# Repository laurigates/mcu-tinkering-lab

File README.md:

# MCU Tinkering Lab

A monorepo of microcontroller projects, mostly ESP32. The largest is a robot car
that drives on camera input and an LLM's plan. Others cover audio toys, game
controller bridges, an ESP-NOW mesh of companion boxes, and a self-balancing
robot on the RP2350.

## Flash from the browser

Released firmware can be flashed with the
[web flasher](https://laurigates.github.io/mcu-tinkering-lab/) in Chrome or
Edge, with no toolchain installed. Board-specific boot-mode notes are on the
page itself ([source](docs/flasher/index.html)).

The [robocar board story](https://laurigates.github.io/mcu-tinkering-lab/robocar/)
follows the robot car from a 2018 kit to a generated, factory-made carrier
board ([source](docs/site/robocar/index.html)).

## Build from source

ESP-IDF builds run in a container, so Docker and
[just](https://github.com/casey/just) are the only requirements.

```bash
git clone https://github.com/laurigates/mcu-tinkering-lab.git
cd mcu-tinkering-lab
just setup-all                   # Docker images, dev tools, pre-commit hooks
just list-projects               # every project module
just robocar::build              # build one
```

Build, test and CI details are in [CONTRIBUTING.md](CONTRIBUTING.md).

## Projects

| Domain | Projects |
|---|---|
| `robotics/` | [AI robot car](packages/robotics/robocar/README.md): single-board firmware (XIAO ESP32-S3 Sense), its [integrated carrier](packages/robotics/robocar/integrated/README.md), [bring-up self-test](packages/robotics/robocar/bringup/README.md), a [Pymunk plant model](packages/robotics/robocar/simulation/README.md) and a [behaviour twin](packages/robotics/robocar/twin/README.md). [Self-balancing robot](packages/robotics/balancebot/README.md) (XIAO RP2350, Pico SDK) |
| `thinkpack/` | ESP-NOW mesh of companion boxes: brainbox (LLM coordinator), boombox, chatterbox, finderbox, glowbug, mesh-demo |
| `camera-vision/` | MJPEG webserver, camera + I2S audio, LLM Telegram bot, Gemini object detection |
| `audio/` | BLE gamepad synth, kids' audio toy, melody detector, RFID audiobook player (ESPHome) |
| `input-gaming/` | Xbox → Switch bridge, Switch USB proxy, LEGO Boost with an Xbox controller |
| `networking/` | IT troubleshooter, WiFi AP test, WireGuard + Home Assistant (ESPHome) |
| `sensors/` | 24 GHz mmWave presence sensor (ESPHome) |
| `usb-tools/` | ESP32-S3 raw USB relay for facedancer |
| `games/` | NFC scavenger hunt |
| `components/` | Shared ESP-IDF components: Improv WiFi provisioning, GitHub Releases OTA, ThinkPack libraries |

Most projects have a README in their directory.

## Documentation

- [docs/](docs/README.md): architecture decisions, requirements, board
  references, schematics
- [CONTRIBUTING.md](CONTRIBUTING.md): development setup, build commands,
  testing, CI, adding a project

## License

MIT ([LICENSE](LICENSE)), except the two vendored KiCad libraries under
`tools/kicad/lib/`, which keep their upstream licences:
[`kicad-stock/`](tools/kicad/lib/kicad-stock/) is a subset of the KiCad
libraries under CC-BY-SA 4.0 with KiCad's design exception
([LICENSE.md](tools/kicad/lib/kicad-stock/LICENSE.md)), and
[`seeed-xiao/`](tools/kicad/lib/seeed-xiao/) is Seeed Studio's, under their MIT
licence ([LICENSE](tools/kicad/lib/seeed-xiao/LICENSE)).

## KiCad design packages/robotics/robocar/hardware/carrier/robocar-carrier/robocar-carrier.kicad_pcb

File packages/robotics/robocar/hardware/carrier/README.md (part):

# robocar carrier PCB

> **Before paying for an order**, Lauri does the bench checks in
> [Pre-order checks still owed](#pre-order-checks-still-owed-lauri);
> [`board.toml`](board.toml) marks every unmeasured dimension (#750).

One 100 × 100 mm, 2-layer PCB that carries four pieces and replaces the
hand-wired harness in [`WIRING.md`](../../WIRING.md):

- the **main board**, x 0–70.5 mm, screwed to the chassis (no ready-made plate; the chassis is drilled to match H1–H4): the motor driver,
  the PWM driver, the I2C mux, the GPIO expander and its mirror header, the
  amplifier, the 3V3 regulator, the power and peripheral connectors, the
  buzzer and the test headers;
- three **head boards** in a column on its right, each 29.5 × 29.5 mm, for the
  pan-tilt kit's top cradle: a XIAO ESP32-S3 Sense socket and the head end of
  the ribbon. They differ only in where the ribbon header sits (see
  [The three heads](#the-three-heads)); fit the XIAO to the one that suits the
  cradle.

Copper-free bands of 3 mm or more under silkscreen saw lines ("CUT", on both
faces) separate the pieces. JLCPCB makes one rectangle with no V-cuts, tabs or
slots; the pieces are sawn apart after delivery (see
[Separating the pieces](#separating-the-pieces)). A 2 × 7, 2.0 mm-pitch IDC
ribbon joins the main board to the fitted head.

KiCad 10 project: [`robocar-carrier/`](robocar-carrier/). Its
schematic is generated from [`hardware.toml`](../../hardware.toml) and the parts
registry ([`docs/reference/parts/`](../../../../../docs/reference/parts/)) by
`tools/kicad`
([ADR-027](../../../../../docs/decisions/ADR-027-kicad-carrier-generation.md));
the board is placed and routed from the same netlist and
[`board.toml`](board.toml), which holds every position, the bands and the
silkscreen. Never edit the `.kicad_sch` or `.kicad_pcb` in KiCad; change those
files and regenerate (see [Regenerate and check](#regenerate-and-check)).

## What is on it

Each module sits in female headers or plugs into a connector, so any of them can
be swapped without desoldering. The passives and the regulator are SMD on the
top side; everything else is through-hole.

| Ref | Part | Board | Notes |
|---|---|---|---|
| U1, U3, U4 | XIAO ESP32-S3 Sense socket, two 1×7 female headers | heads 1, 2, 3 | USB-C toward the head's top edge; fit one XIAO |
| J2, J16, J17 | 2×7 pin header, 2.0 mm, unshrouded | heads 1, 2, 3 | The head end of the ribbon; see [The three heads](#the-three-heads) |
| H5–H10 | M2 holes, 2.2 mm, ISO 7380 courtyard | heads 1, 2, 3 | Through the cradle into heat-set inserts; M2 button heads only |
| J1 | 2×7 pin header, 2.0 mm, unshrouded | main | The main end of the ribbon, in the front row; its pins are 21–33 mm in from the main board's right edge. Lauri's 10–15 cm ribbon length was for J1's earlier spot beside the head column, so check it still reaches |
| A1 | SparkFun TB6612FNG, in 2 × 1×8 female headers | main | Motor outputs on its left header |
| A2 | Adafruit PCA9685, in female headers on its JP3 side header and its channel 8–13 PWM pins | main | Motor control lines; servo and LED columns stay on the module |
| A3 | Adafruit TCA9548A, or the wider purple TCA9548A/PCA9548A clone, in female headers | main | Every I2C device sits behind it. The clone's rows are one pitch wider, so the upstream (VIN…SC1) side has a second row of holes one pitch toward the rear, each joined to the hole beside it; see [The TCA9548A socket](#the-tca9548a-socket) |
| A4 | Adafruit MAX98357A, in a 1×7 female header | main | The speaker stays on the module's terminal |
| A5 | CJMCU-2317 (MCP23017), in female headers under all 30 holes | main | On mux channel 2, address 0x20; see [The GPIO expander](#the-gpio-expander) |
| J18 | 2×10 pin header, 2.54 mm | main | The expander's GPIOs, in the module's own order; see [The GPIO expander](#the-gpio-expander) |
| U2 | AMS1117-3.3, SOT-223 | main | The main board's 3V3; the XIAO's 3V3 pad stays open |
| D1 | B5819W Schottky, SOD-123 | main | Between the main board's 5V and the ribbon's 5V conductors (net `XIAO_5V`), beside J1: the XIAO's 5V pad is its USB-C VBUS |
| C1–C3 | 470 µF 16 V electrolytic, 8 × 10.5 mm | main | Bulk on the 5V trunk for the PCA9685 V+ and TB6612FNG VM (C1, C2), and beside the MAX98357A Vin (C3) |
| C4–C6 | 100 nF, 0805 | main | PCA9685 VCC, TCA9548A VIN, MCP23017 VCC (C6, beside the CJMCU-2317's socket) |
| C7, C8 | 22 µF 16 V tantalum, 3528 | main | AMS1117 input and output |
| R1 | 100 Ω, 0805 | main | Buzzer series resistor |
| R2–R11 | 2.2 kΩ, 0805 | main | Pull-ups on mux channels 0–4 (R10, R11 on channel 2); see [Pre-fab review](#pre-fab-review-810) |
| R12, R13 | 2.2 kΩ, 0805 | main | Pull-ups on the upstream I2C bus (the XIAO's SDA and SCL), beside C5 in the row behind A3 |
| F1 | 4 A hold PTC fuse, 16 V, 1812 (BSMD1812-400-16V) | main | Between J3 and everything else, beside J3 |
| J3 | XT30 (AMASS XT30PW-M) | main | Pack in; pad 1 is "−" |
| J4 | JST VH 4-pin (B4P-VH), 3.96 mm | main | LM2596 module: IN+, IN−, OUT+, OUT−; the silkscreen prints "I+ I- O+ O-" and "SET LM2596 TO 5.0V FIRST" beside it |
| J5, J6 | JST-XH 2-pin | main | Left and right motor, side by side at A1's motor outputs |
| J7, J8 | JST-XH 4-pin | main | RCWL-1601 front and rear, I2C mode: VCC, SCL, SDA, GND (silkscreen "V C D G"); side by side at the front edge |
| J9 | JST-XH 4-pin | main | SSD1306 0.91" OLED: GND, VCC, SCL, SDA (silkscreen "G V C D") |
| BZ1 | 12 mm buzzer, 7.6 mm pin pitch | main | Soldered to the board; + on pad 1, beside the silkscreen "+" |
| J11–J15 | 1×4 and 1×2 pin headers | main | Test headers, see [Debug headers](#debug-headers) |
| H1–H4 | M3 holes | main | Chassis (drilled to match) |

The per-part values, LCSC numbers and the reasons for each are in
[`hardware.toml`](../../hardware.toml); the pin orders are in the registry entries
it names.

## The three heads

All three have the same outline, the same two M2 holes in the top corners
(22.5 mm apart, the positions Lauri confirmed on 2026-10-16), and the XIAO with
its USB-C toward the top edge, which points the Sense camera forward. The
cradle's sides carry clips, so the header sits at the top or the bottom edge,
never at a side (Lauri, 2026-10-16). Only one head gets a XIAO; the other two
stay spare.

| Head | Refs | Header | XIAO | For |
|---|---|---|---|---|
| 1 | U1, J2, H5, H6 | Back face, bottom edge | Between the holes, above the header | The plug and ribbon behind the head, leaving the bottom edge |
| 2 | U3, J16, H7, H8 | Front face, bottom edge | Between the holes, above the header | The plug in front, below the camera, if nothing behind the head clears it |
| 3 | U4, J17, H9, H10 | Back face, top edge, between the holes | Below the holes | The ribbon leaving over the top, if the bottom edge is blocked |

The holes use KiCad's ISO 7380 M2 footprint, whose courtyard is a 3.5 mm button
head: on heads 1 and 2 the XIAO socket sits 0.26 mm from it on each side. Fit
M2 button-head screws (ISO 7380) or another head no larger than 3.5 mm.

Each head's spare copy of the XIAO socket is wired to its own header (nets
`HEAD2_*`, `HEAD3_*`); the main board has a single end, J1. Moving the ribbon
to another head moves the robot to it.

## The ribbon survives a reversed plug

The headers are unshrouded 2.0 mm-pitch pin headers, mated by a 2.0 mm IDC plug
on 1.0 mm-pitch flat ribbon. The plug fits either way round, which takes
pin *n* to pin 15 − *n*. The pinout in
[`idc-2x07-xiao-cable.toml`](../../../../../docs/reference/parts/idc-2x07-xiao-cable.toml)
pairs each pin with one it can safely swap with: 5 V lands on 5 V, GND on GND,
SDA on SCL, UART0 TX on the unconnected pin 9, and every other XIAO output on
another main-board input. **A reversed plug damages nothing and does not work.**
If the robot is dead after reassembly, check the plug orientation first: every
header prints a pin-1 mark.

## The GPIO expander

The CJMCU-2317 module (A5) sits in female headers under all 30 of its holes,
so it plugs in firmly and every pin reaches the board. It is turned 180°: its
single column (I2C and supply) faces the mux, its double column of GPIOs faces
the right edge. Hole positions and which column is which are Lauri's
measurement of the fitted module (2026-10-16), recorded on
[its board page](../../../../../docs/reference/boards/cjmcu-2317.md).
It fits upside down too, which shorts 3V3: fit it chip side up (see
[Assembly notes](#assembly-notes)). The silkscreen inside its socket outline
names every hole, and "CHIP SIDE UP" is printed below it.

- **Address 0x20, hard-strapped.** A0, A1 and A2 go straight to GND, which is
  `MCP23017_ADDR` in [`main/pin_config.h`](../../main/pin_config.h). A direct
  tie overrides whatever bias the module itself puts on those pins.
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
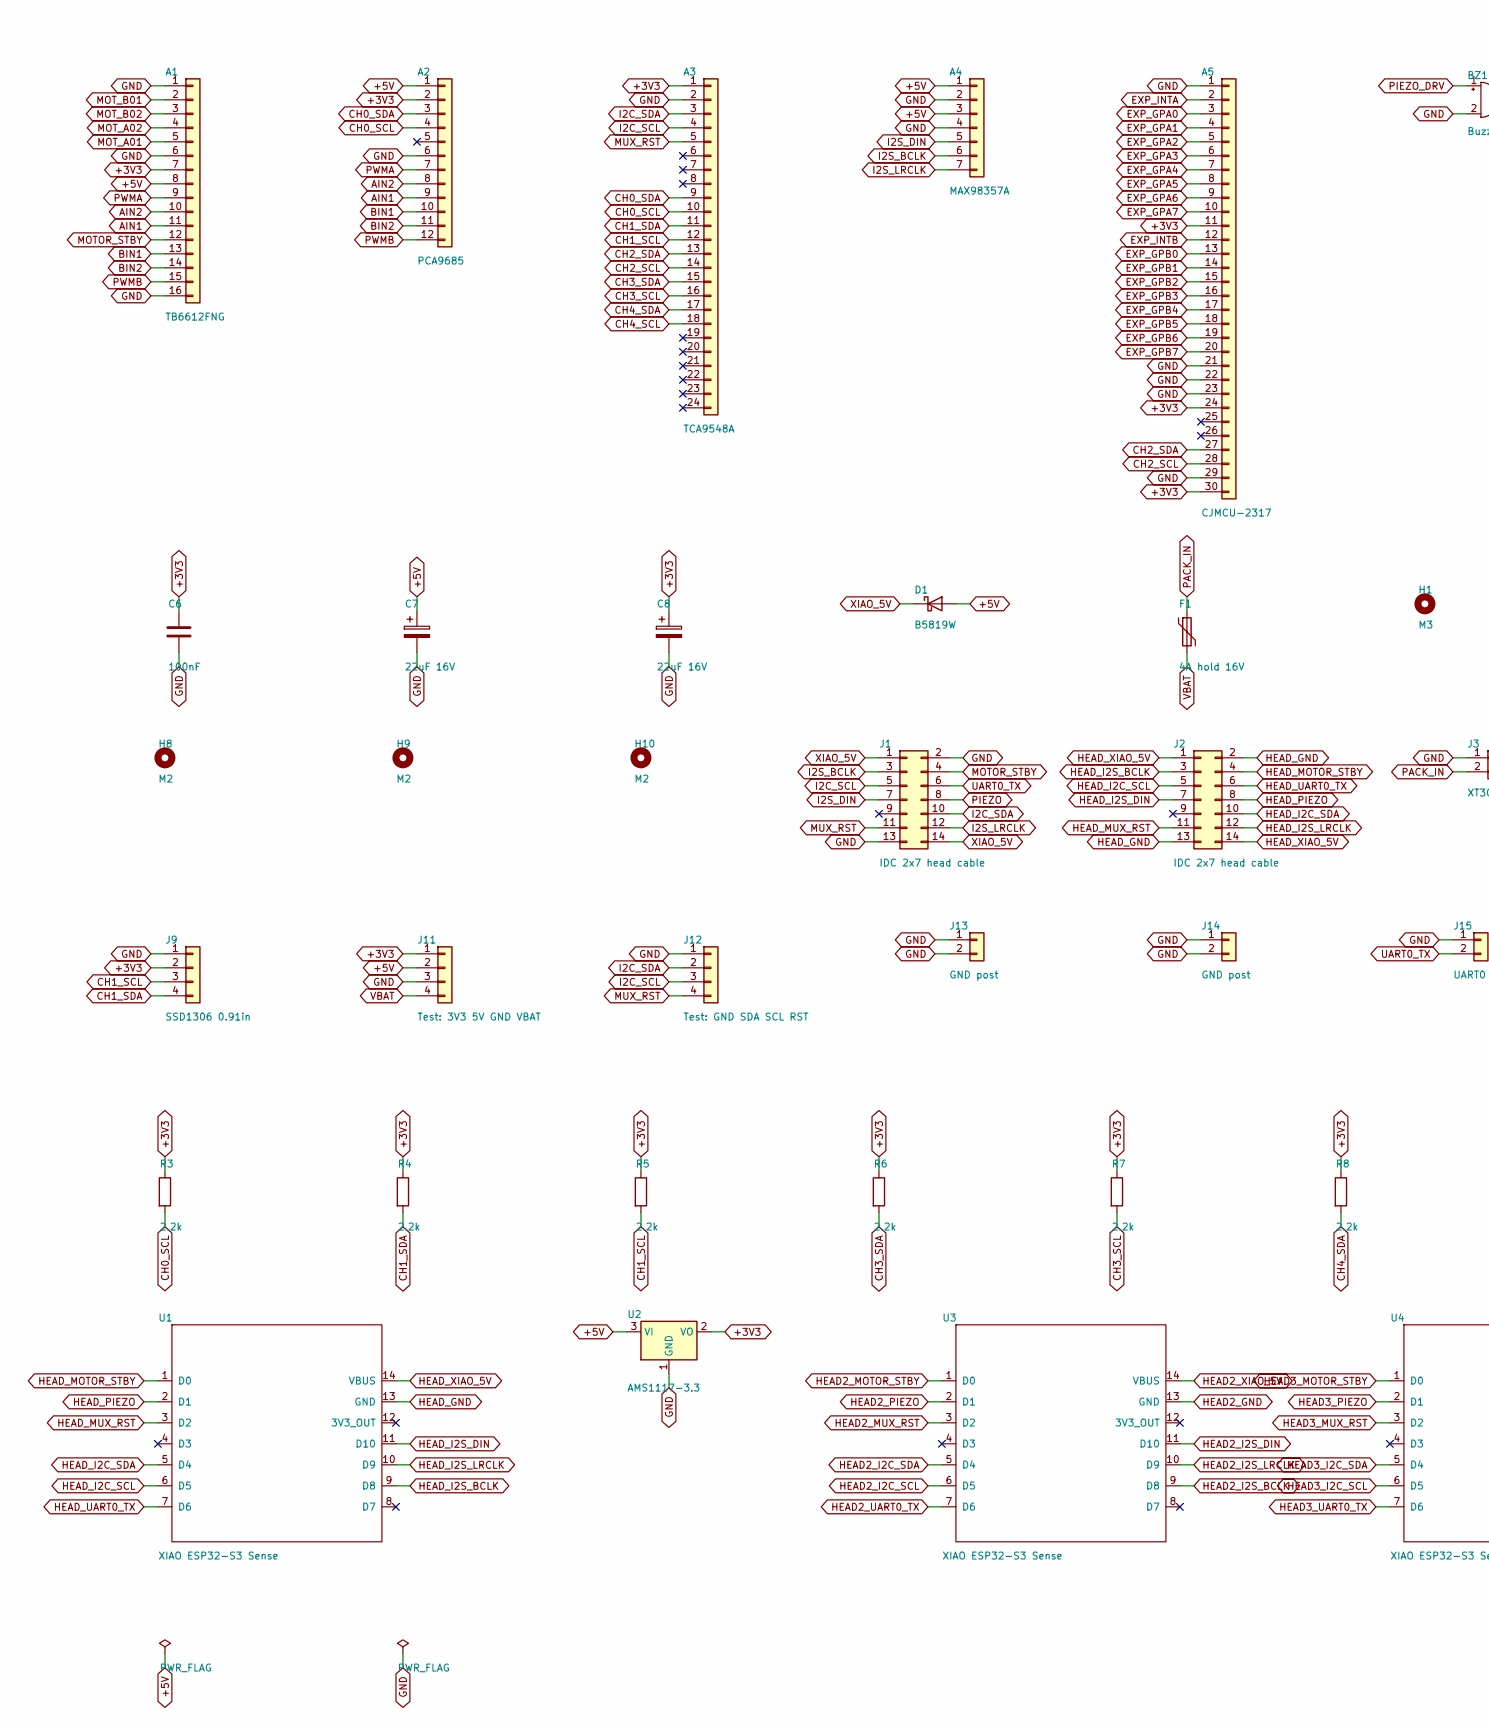
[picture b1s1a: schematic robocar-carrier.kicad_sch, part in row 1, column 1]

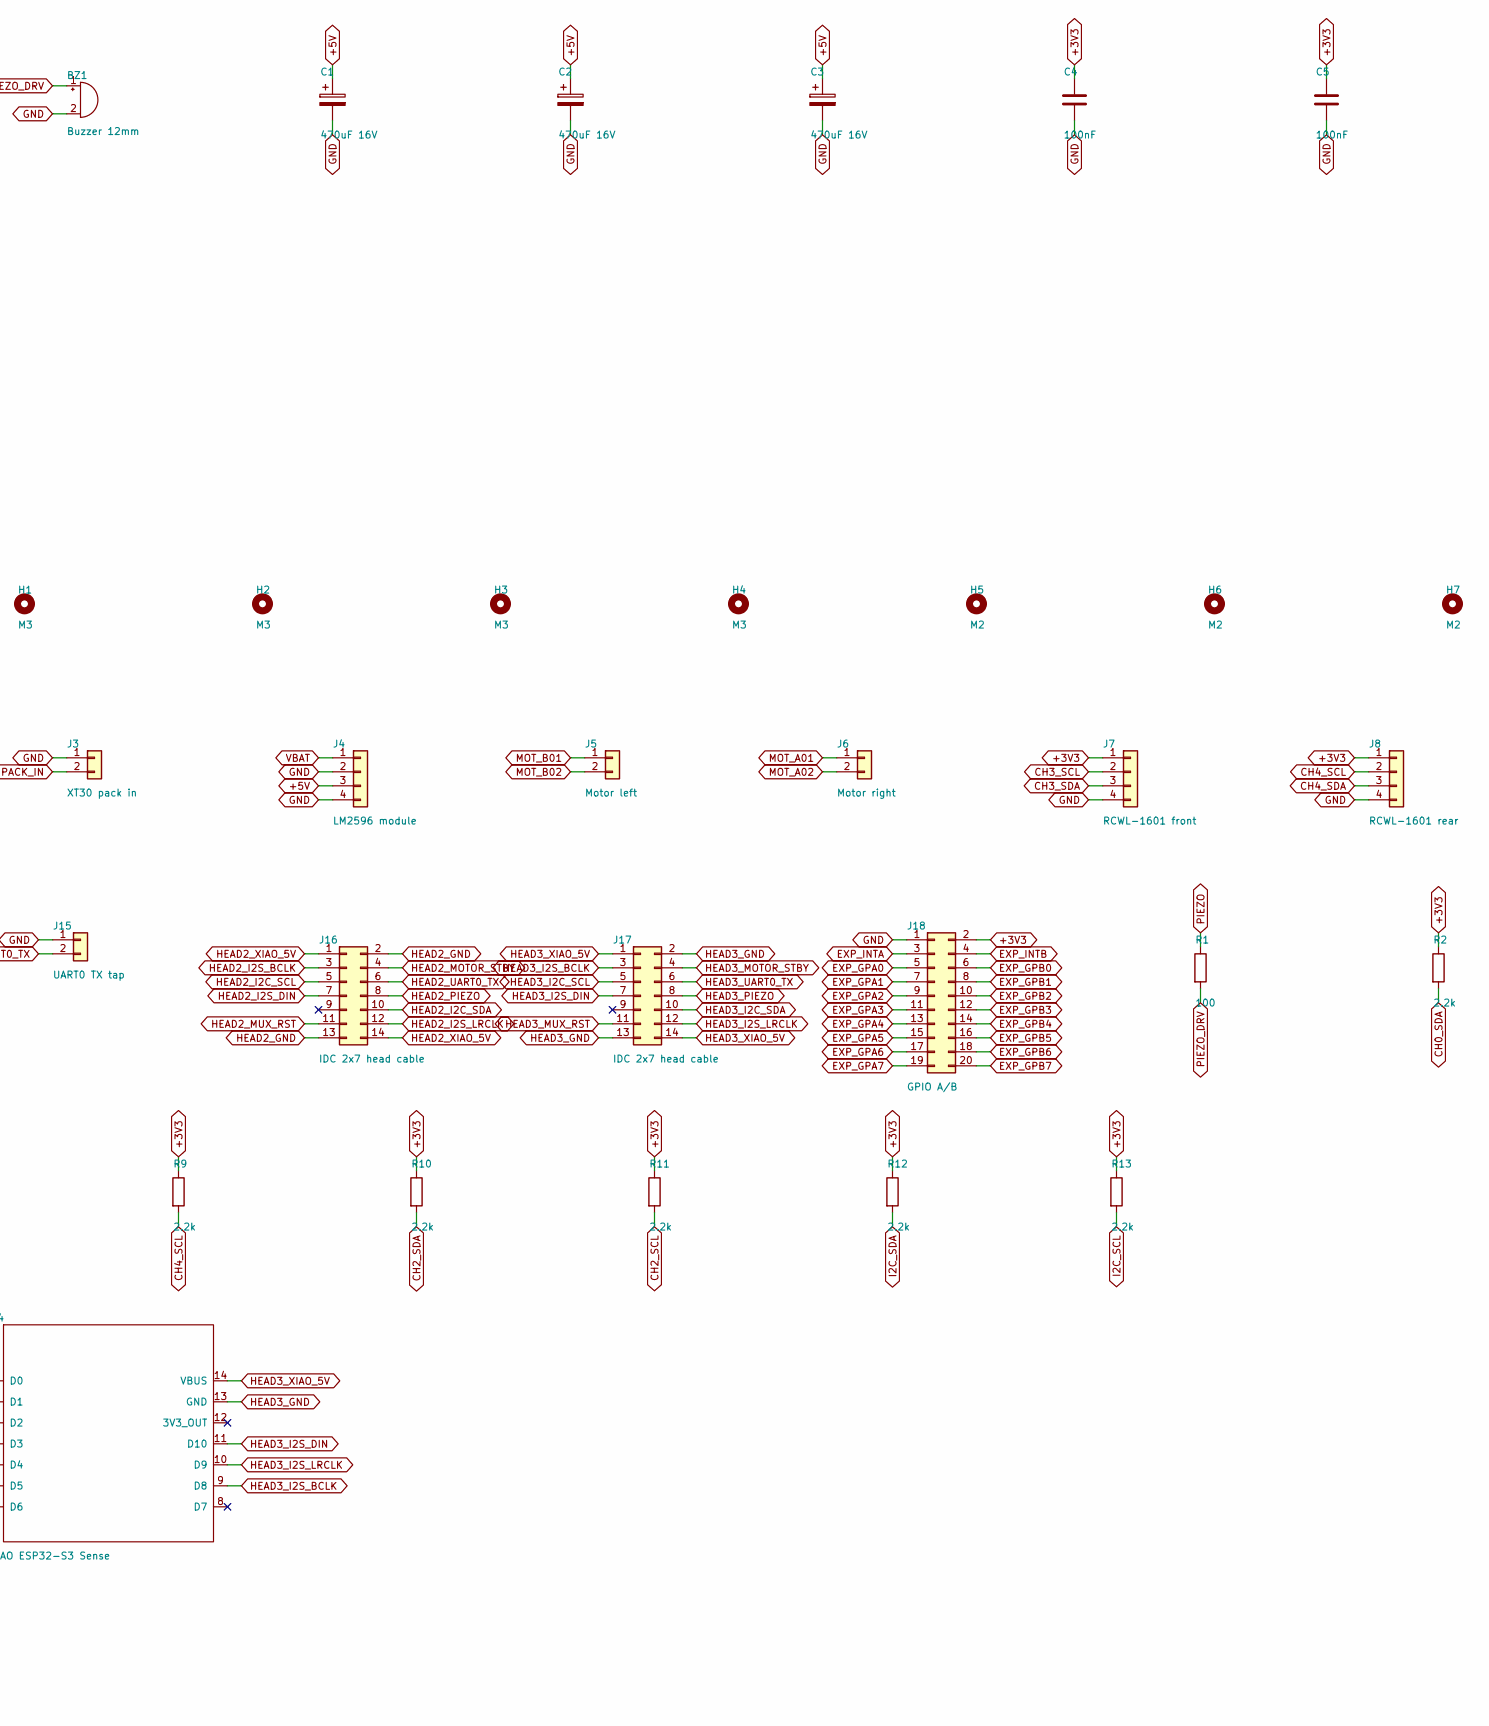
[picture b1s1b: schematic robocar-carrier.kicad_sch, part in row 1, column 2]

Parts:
A1: TB6612FNG; SparkFun_TB6612FNG_Socket
A2: PCA9685; Adafruit_PCA9685_Socket
A3: TCA9548A; Adafruit_TCA9548A_Socket
A4: MAX98357A; Adafruit_MAX98357A_Socket
A5: CJMCU-2317; CJMCU_2317_Socket
BZ1: Buzzer 12mm; Buzzer_12x9.5RM7.6
C1, C2, C3: 470uF 16V; CP_Elec_8x10.5; LCSC C96179
C4, C5, C6: 100nF; C_0805_2012Metric_Pad1.18x1.45mm_HandSolder; LCSC C49678
C7, C8: 22uF 16V; CP_EIA-3528-21_Kemet-B_HandSolder; LCSC C8020
D1: B5819W; D_SOD-123; LCSC C8598
F1: 4A hold 16V; Fuse_1812_4532Metric_Pad1.30x3.40mm_HandSolder; LCSC C47263807
H1, H2, H3, H4: M3; MountingHole_3.2mm_M3
H5, H6, H7, H8, H9, H10: M2; MountingHole_2.2mm_M2_ISO7380
J1, J2, J16, J17: IDC 2x7 head cable; PinHeader_2x07_P2.00mm_Vertical
J3: XT30 pack in; AMASS_XT30PW-M_1x02_P2.50mm_Horizontal
J4: LM2596 module; JST_VH_B4P-VH_1x04_P3.96mm_Vertical
J5: Motor left; JST_XH_B2B-XH-A_1x02_P2.50mm_Vertical
J6: Motor right; JST_XH_B2B-XH-A_1x02_P2.50mm_Vertical
J7: RCWL-1601 front; JST_XH_B4B-XH-A_1x04_P2.50mm_Vertical
J8: RCWL-1601 rear; JST_XH_B4B-XH-A_1x04_P2.50mm_Vertical
J9: SSD1306 0.91in; JST_XH_B4B-XH-A_1x04_P2.50mm_Vertical
J11: Test: 3V3 5V GND VBAT; PinHeader_1x04_P2.54mm_Vertical
J12: Test: GND SDA SCL RST; PinHeader_1x04_P2.54mm_Vertical
J13, J14: GND post; PinHeader_1x02_P2.54mm_Vertical
J15: UART0 TX tap; PinHeader_1x02_P2.54mm_Vertical
J18: GPIO A/B; PinHeader_2x10_P2.54mm_Vertical
R1: 100; R_0805_2012Metric_Pad1.20x1.40mm_HandSolder; LCSC C17408
R2, R3, R4, R5, R6, R7, R8, R9, R10, R11, R12, R13: 2.2k; R_0805_2012Metric_Pad1.20x1.40mm_HandSolder; LCSC C17520
U1, U3, U4: XIAO ESP32-S3 Sense; XIAO-ESP32-S3-Socket
U2: AMS1117-3.3; SOT-223-3_TabPin2; LCSC C6186

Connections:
+3V3: A1.7, A2.2, A3.1, A5.11, A5.24, A5.30, C4.1, C5.1, C6.1, C8.1, J7.1, J8.1, J9.2, J11.1, J18.2, R2.1, R3.1, R4.1, R5.1, R6.1, R7.1, R8.1, R9.1, R10.1, R11.1, R12.1, R13.1, U2.2 (VO)
+5V: A1.8, A2.1, A4.1, A4.3, C1.1, C2.1, C3.1, C7.1, D1.2 (A), J4.3, J11.2, U2.3 (VI)
AIN1: A1.11, A2.9
AIN2: A1.10, A2.8
BIN1: A1.13, A2.10
BIN2: A1.14, A2.11
CH0_SCL: A2.4, A3.10, R3.2
CH0_SDA: A2.3, A3.9, R2.2
CH1_SCL: A3.12, J9.3, R5.2
CH1_SDA: A3.11, J9.4, R4.2
CH2_SCL: A3.14, A5.28, R11.2
CH2_SDA: A3.13, A5.27, R10.2
CH3_SCL: A3.16, J7.2, R7.2
CH3_SDA: A3.15, J7.3, R6.2
CH4_SCL: A3.18, J8.2, R9.2
CH4_SDA: A3.17, J8.3, R8.2
EXP_GPA0: A5.3, J18.5
EXP_GPA1: A5.4, J18.7
EXP_GPA2: A5.5, J18.9
EXP_GPA3: A5.6, J18.11
EXP_GPA4: A5.7, J18.13
EXP_GPA5: A5.8, J18.15
EXP_GPA6: A5.9, J18.17
EXP_GPA7: A5.10, J18.19
EXP_GPB0: A5.13, J18.6
EXP_GPB1: A5.14, J18.8
EXP_GPB2: A5.15, J18.10
EXP_GPB3: A5.16, J18.12
EXP_GPB4: A5.17, J18.14
EXP_GPB5: A5.18, J18.16
EXP_GPB6: A5.19, J18.18
EXP_GPB7: A5.20, J18.20
EXP_INTA: A5.2, J18.3
EXP_INTB: A5.12, J18.4
GND: A1.1, A1.6, A1.16, A2.6, A3.2, A4.2, A4.4, A5.1, A5.21, A5.22, A5.23, A5.29, BZ1.2 (-), C1.2, C2.2, C3.2, C4.2, C5.2, C6.2, C7.2, C8.2, J1.2, J1.13, J3.1, J4.2, J4.4, J7.4, J8.4, J9.1, J11.3, J12.1, J13.1, J13.2, J14.1, J14.2, J15.1, J18.1, U2.1 (GND)
HEAD2_GND: J16.2, J16.13, U3.13 (GND)
HEAD2_I2C_SCL: J16.5, U3.6 (D5)
HEAD2_I2C_SDA: J16.10, U3.5 (D4)
HEAD2_I2S_BCLK: J16.3, U3.9 (D8)
HEAD2_I2S_DIN: J16.7, U3.11 (D10)
HEAD2_I2S_LRCLK: J16.12, U3.10 (D9)
HEAD2_MOTOR_STBY: J16.4, U3.1 (D0)
HEAD2_MUX_RST: J16.11, U3.3 (D2)
HEAD2_PIEZO: J16.8, U3.2 (D1)
HEAD2_UART0_TX: J16.6, U3.7 (D6)
HEAD2_XIAO_5V: J16.1, J16.14, U3.14 (VBUS)
HEAD3_GND: J17.2, J17.13, U4.13 (GND)
HEAD3_I2C_SCL: J17.5, U4.6 (D5)
HEAD3_I2C_SDA: J17.10, U4.5 (D4)
HEAD3_I2S_BCLK: J17.3, U4.9 (D8)
HEAD3_I2S_DIN: J17.7, U4.11 (D10)
HEAD3_I2S_LRCLK: J17.12, U4.10 (D9)
HEAD3_MOTOR_STBY: J17.4, U4.1 (D0)
HEAD3_MUX_RST: J17.11, U4.3 (D2)
HEAD3_PIEZO: J17.8, U4.2 (D1)
HEAD3_UART0_TX: J17.6, U4.7 (D6)
HEAD3_XIAO_5V: J17.1, J17.14, U4.14 (VBUS)
HEAD_GND: J2.2, J2.13, U1.13 (GND)
HEAD_I2C_SCL: J2.5, U1.6 (D5)
HEAD_I2C_SDA: J2.10, U1.5 (D4)
HEAD_I2S_BCLK: J2.3, U1.9 (D8)
HEAD_I2S_DIN: J2.7, U1.11 (D10)
HEAD_I2S_LRCLK: J2.12, U1.10 (D9)
HEAD_MOTOR_STBY: J2.4, U1.1 (D0)
HEAD_MUX_RST: J2.11, U1.3 (D2)
HEAD_PIEZO: J2.8, U1.2 (D1)
HEAD_UART0_TX: J2.6, U1.7 (D6)
HEAD_XIAO_5V: J2.1, J2.14, U1.14 (VBUS)
I2C_SCL: A3.4, J1.5, J12.3, R13.2
I2C_SDA: A3.3, J1.10, J12.2, R12.2
I2S_BCLK: A4.6, J1.3
I2S_DIN: A4.5, J1.7
I2S_LRCLK: A4.7, J1.12
MOTOR_STBY: A1.12, J1.4
MOT_A01: A1.5, J6.1
MOT_A02: A1.4, J6.2
MOT_B01: A1.2, J5.1
MOT_B02: A1.3, J5.2
MUX_RST: A3.5, J1.11, J12.4
PACK_IN: F1.1, J3.2
PIEZO: J1.8, R1.1
PIEZO_DRV: BZ1.1 (+), R1.2
PWMA: A1.9, A2.7
PWMB: A1.15, A2.12
UART0_TX: J1.6, J15.2
VBAT: F1.2, J4.1, J11.4
XIAO_5V: D1.1 (K), J1.1, J1.14

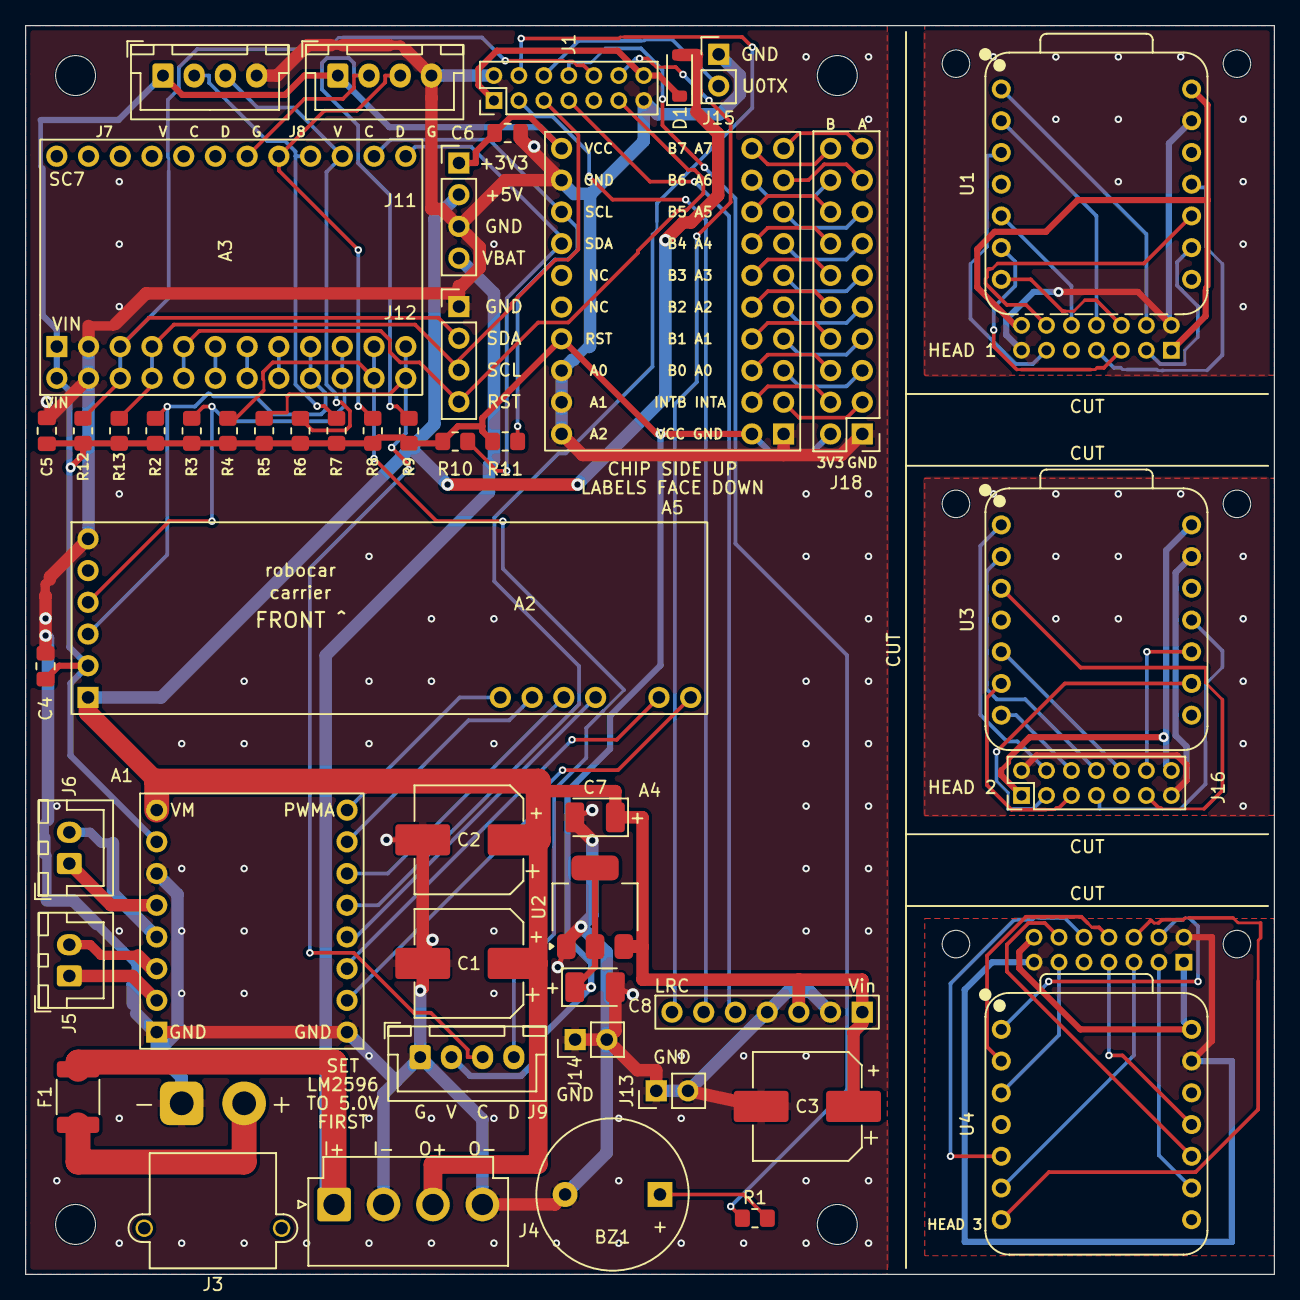
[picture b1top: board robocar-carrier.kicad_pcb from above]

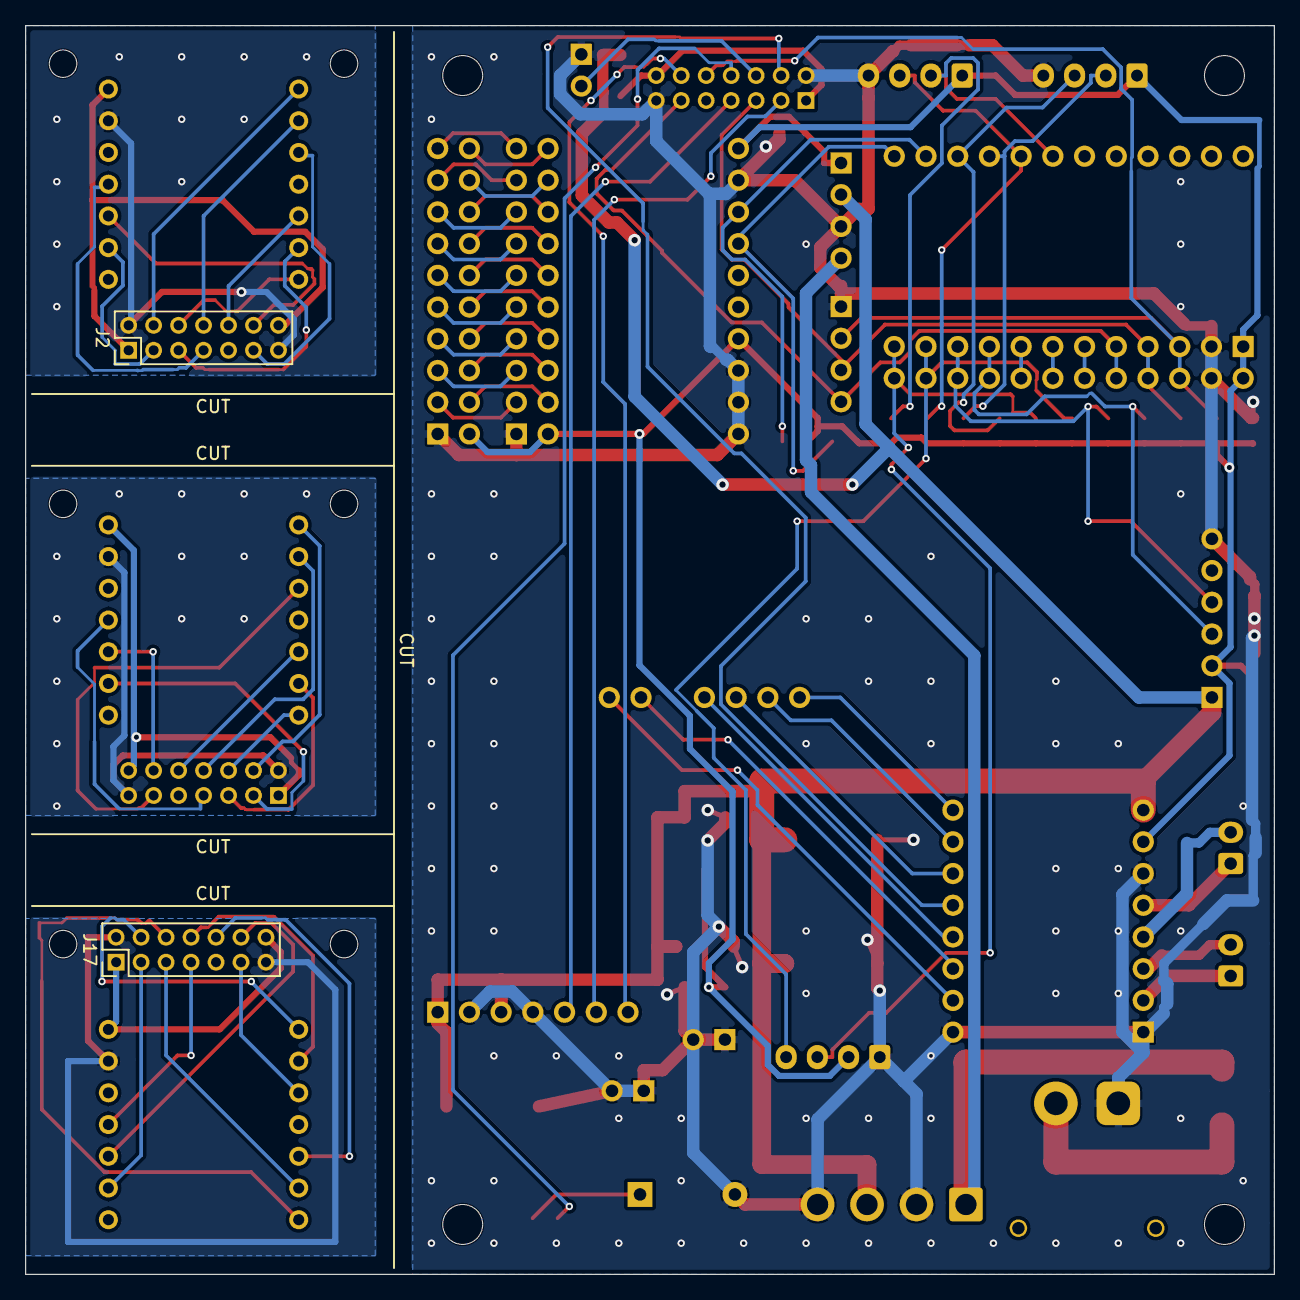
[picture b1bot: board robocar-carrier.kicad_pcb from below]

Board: 2 copper layers, 100.0 x 100.0 mm, 60 parts (2 on the bottom side), 87 nets.

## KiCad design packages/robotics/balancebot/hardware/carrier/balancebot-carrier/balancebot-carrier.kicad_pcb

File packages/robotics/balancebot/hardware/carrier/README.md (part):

# Balancebot carrier PCB

A 90 × 62 mm, 2-layer carrier that replaces the hand-wired harness in
[`WIRING.md`](../../WIRING.md). Every module sits in a socket or plugs into a
connector, so any of them can be swapped without desoldering. The passives are
SMD on the top side; the sockets and connectors are through-hole.

KiCad 10 project: [`balancebot-carrier/`](balancebot-carrier/). Its schematic is
generated from [`hardware.toml`](../../hardware.toml) and the parts registry
([`docs/reference/parts/`](../../../../../docs/reference/parts/)) by `tools/kicad`
([ADR-027](../../../../../docs/decisions/ADR-027-kicad-carrier-generation.md)):
never edit `balancebot-carrier.kicad_sch` in KiCad; change `hardware.toml` or a
registry entry and regenerate. The board is placed and routed from the same
netlist and [`board.toml`](board.toml) (placement, silkscreen, net classes, pour).

## Revision

This is **rev3** (2026-11), printed "rev3 2026-11" beside the board's title.
It adds the expansion header J6 with its 5V diode D3 and series resistors R5
and R6, the drivers' VIO links R7 and R8, the I2C tap J7, the supply test header J8 and the
ground post J9, and changes R3 from 27 kΩ to 22 kΩ so D0 can read a 4S pack.

Since 2026-11-09 J3 is the generated `Breakout_Sockets:GY521_Socket`, whose
F.Fab outline puts the module in front of the header. Its pads are where the
plain 1×8 socket's were, and the re-route laid every track where it was
before. The silkscreen no longer has the hand-drawn rectangle where the module
lies; "GY-521: X arrow to FWD" stays. The module outline is back on F.SilkS,
drawn from the footprint's F.Fab (`[silk] module_outlines`; its rear edge is
the socket strip's own outline), with VCC left of pin 1 and INT below pin 8.
`kicad.orientation` holds every module socket to having such marks: J3 fits
its socket three wrong ways (turned 180°, flipped end to end, or face down
across the row), A1 and A2 three each. `carrier-silk` added them with the copper
unchanged (same 247 track segments, 95 vias, 2 zones and 32 footprints).

The boards delivered from the 2026-10-23 order (JLCPCB W2026102320533303,
PCB line Y5-13829495A, file `balancebot-carrier-fab_Y5`) are the
**commit 8d18cd8d layout** (#753, 2026-10-13), not the board this README
described until rev3. JLCPCB built Y5, an upload left in the cart since
13–14 October. The order history's thumbnail of Y5 matches a render of
8d18cd8d: XT30 J1, J3 at the front edge of the GY-521 outline, no F1, Q1,
D2 or R4, and no stitching vias. The delivered boards, inspected by hand,
lack the F1, Q1, D2 and R4 footprints. The 2026-10-23 hand-off CSV
attributed that line to `main@9735477d` because it recorded the zip on disk,
not the file JLCPCB had in the cart.

- **8d18cd8d, the delivered boards:** XT30 J1, pad 1 GND and pad 2 VBAT,
  with no polarity printed; 7 SMD parts (R1–R3, C1–C3, D1) and no F1, Q1, D2
  or R4, so no fuse and no reverse-polarity protection; R3 27 kΩ (ratio
  27/127). J3 is on the front edge of the GY-521 outline (board y 33). Fitted
  component side up, the module's pins land reversed (VCC on INT), so it is
  fitted component side down, hanging rearward: the wiring is then correct,
  but accel X and Z read inverted (a 180° turn about Y). The firmware computes
  pitch with X forward and Z up (`src/balance_control.c`), so this layout
  needs an IMU-flip option before it can balance.
- **684bb7de** (#822, 2026-10-21) and **6d4aaa68** (#770, 2026-10-14): JST-XH
  J1 layouts in git history that were never fabricated. 684bb7de adds F1, Q1,
  D2 and R4 (11 SMD parts); its R3 is 27 kΩ, so a 4S pack would put 3.57 V on
  D0.

Everything below describes rev3.

## What is on it

| Ref | Part | Connects |
|---|---|---|
| U1 | Seeed XIAO RP2350, in two 1×7 female headers | USB-C toward the top edge |
| A1, A2 | Pololu-format DRV8825 carriers, in 1×8 female headers | Left / right stepper |
| J3 | GY-521 (MPU6050), in a 1×8 female header | Lies flat, component side up, in front of the header (toward FWD); the header is on its rear edge |
| J1 | JST-XH 2-pin (B2B-XH-A) | 3S pack (through its BMS); BAT+ on pad 1 (the square pad, right), marked "+" below it |
| F1 | 3 A hold PTC, 1812 (BSMD1812-300-24V) | Pack input: limits a short on VBAT |
| Q1 | ZXMP4A16G P-MOSFET, SOT-223 | Reverse-polarity switch: drain (tab) to F1, source to VBAT |
| R4 | 10 kΩ, 0805 | Q1's gate to GND |
| D2 | BZT52C15 15 V zener, SOD-123 | Q1's gate to source: cathode to VBAT, anode to the gate |
| J2 | JST-XH 4-pin | LM2596 module: IN+, IN−, OUT+, OUT− |
| J4, J5 | JST-XH 4-pin | Motor coils A1, A2, B1, B2 |
| C1, C2 | 100 µF 35 V SMD electrolytic, 6.3 × 7.7 mm | VMOT bulk at each driver |
| R1 | 10 kΩ, 0805 | nENABLE pull-up to 3V3 (motors off until firmware drives it low) |
| D1 | B5819W (SMD 1N5819), SOD-123 | LM2596 output → XIAO 5V pad, so USB cannot back-feed the buck |
| R2, R3, C3 | 100 kΩ, 22 kΩ, 100 nF, 0805 | Pack voltage divider into D0 (GPIO26, ADC0); C3 sits at the pin |
| J6 | 1×4 male header | Expansion: 5V (XIAO 5V through D3), GND, D2, D1 (front left) |
| D3 | B5819W, SOD-123 | XIAO 5V → J6's 5V pin, so nothing on the expansion cable can back-feed the board |
| R5, R6 | 1 kΩ, 0805 | In series with D1 and D2 at the XIAO's pins, to J6 |
| R7, R8 | 0805 pads, left open | VIO links: each driver socket's pin 2 to 3V3, between its pin rows |
| J7 | 1×4 male header | I2C tap on the IMU bus, Qwiic order: GND, 3V3, SDA, SCL |
| J8 | 1×5 male header | Supply test points: 3V3, GND, 5V (the buck's output), GND, VBAT |
| J9 | 1×2 male header, both pins GND | Ground post for a scope probe's clip |
| H1–H4 | M3 | Mounting holes on a 82 × 54 mm rectangle |

The DRV8825 straps are on the board: M0 and M1 to 3V3 and M2 to GND (1/8
microstep), nSLEEP and nRESET to 3V3, FAULT left open unless its VIO link is
bridged (below). The Pololu carrier has no VDD pin. Pin 2 is FAULT, which
settles the hardware half of #738.

The divider is 100 kΩ over 22 kΩ, a ratio of 0.1803: a full 3S pack (12.6 V)
reads 2.27 V and a full 4S pack (16.8 V) 3.03 V, under the RP2350 ADC's 3.3 V
reference. It draws about 0.1 mA from a 3S pack. Firmware does not read it yet
(#747). The supported pack is 3S: "4S max" on the silkscreen by J1 is the
highest pack the divider can read, not a supported pack. The board's other
parts are chosen for 3S; on 4S, D2 conducts through R4 (below), F1's 24 V
rating leaves 7.2 V over a full pack instead of 11.4 V, and an undamped
hot-plug ring to twice the pack (33.6 V) would reach C1 and C2's 35 V. Before
running 4S, scope a hot-plug at C1 or fit 50 V capacitors in the same
6.3 × 7.7 mm footprint.

### Headers

Each header is a 2.54 mm 1×4 (J8 1×5, J9 1×2), labelled pin by pin on the
silkscreen. Pin 1 is the square pad.

| Header | Pin 1 | Pin 2 | Pin 3 | Pin 4 | Pin 5 | Silkscreen |
|---|---|---|---|---|---|---|
| J6, expansion | EXP_5V (XIAO 5V through D3) | GND | D2 (GPIO28) through R6 | D1 (GPIO27) through R5 | | 5V G TX RX |
| J7, I2C tap | GND | 3V3 | SDA | SCL | | G 3V3 SDA SCL |
| J8, supply test | 3V3 | GND | 5V (BUCK_5V) | GND | VBAT | 3V3 G 5V G VBAT |
| J9, ground post | GND | GND | | | | GND |

- **J6** is for a cable to an ESP-NOW companion XIAO (#960), or a servo's PWM
  or an ADC input; both pins are ADC-capable. XIAO D2 is GPIO28, UART0 TX (GPIO
  function F2), and XIAO D1 is GPIO27, UART1 RX (F11): the silkscreen's TX and
  RX are the RP2350's side, so they cross to the companion's RX and TX. They
  are on two different UARTs, so a hardware-UART link sets up uart0 for TX
  and uart1 for RX (`GPIO_FUNC_UART_AUX`) at one baud rate, or runs a PIO UART
  on PIO1 or PIO2 (PIO0 drives the steppers). 5V sits only beside GND, so a
  lead one pin over cannot put 5V on a GPIO; R5 and R6 (1 kΩ) limit the
  current if the far end drives the same line.
- **J6's 5V pin** is EXP_5V: XIAO_5V (the XIAO's 5V pad, which is its USB-C
  VBUS; [board page](../../../../../docs/reference/boards/xiao-rp2350.md))
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
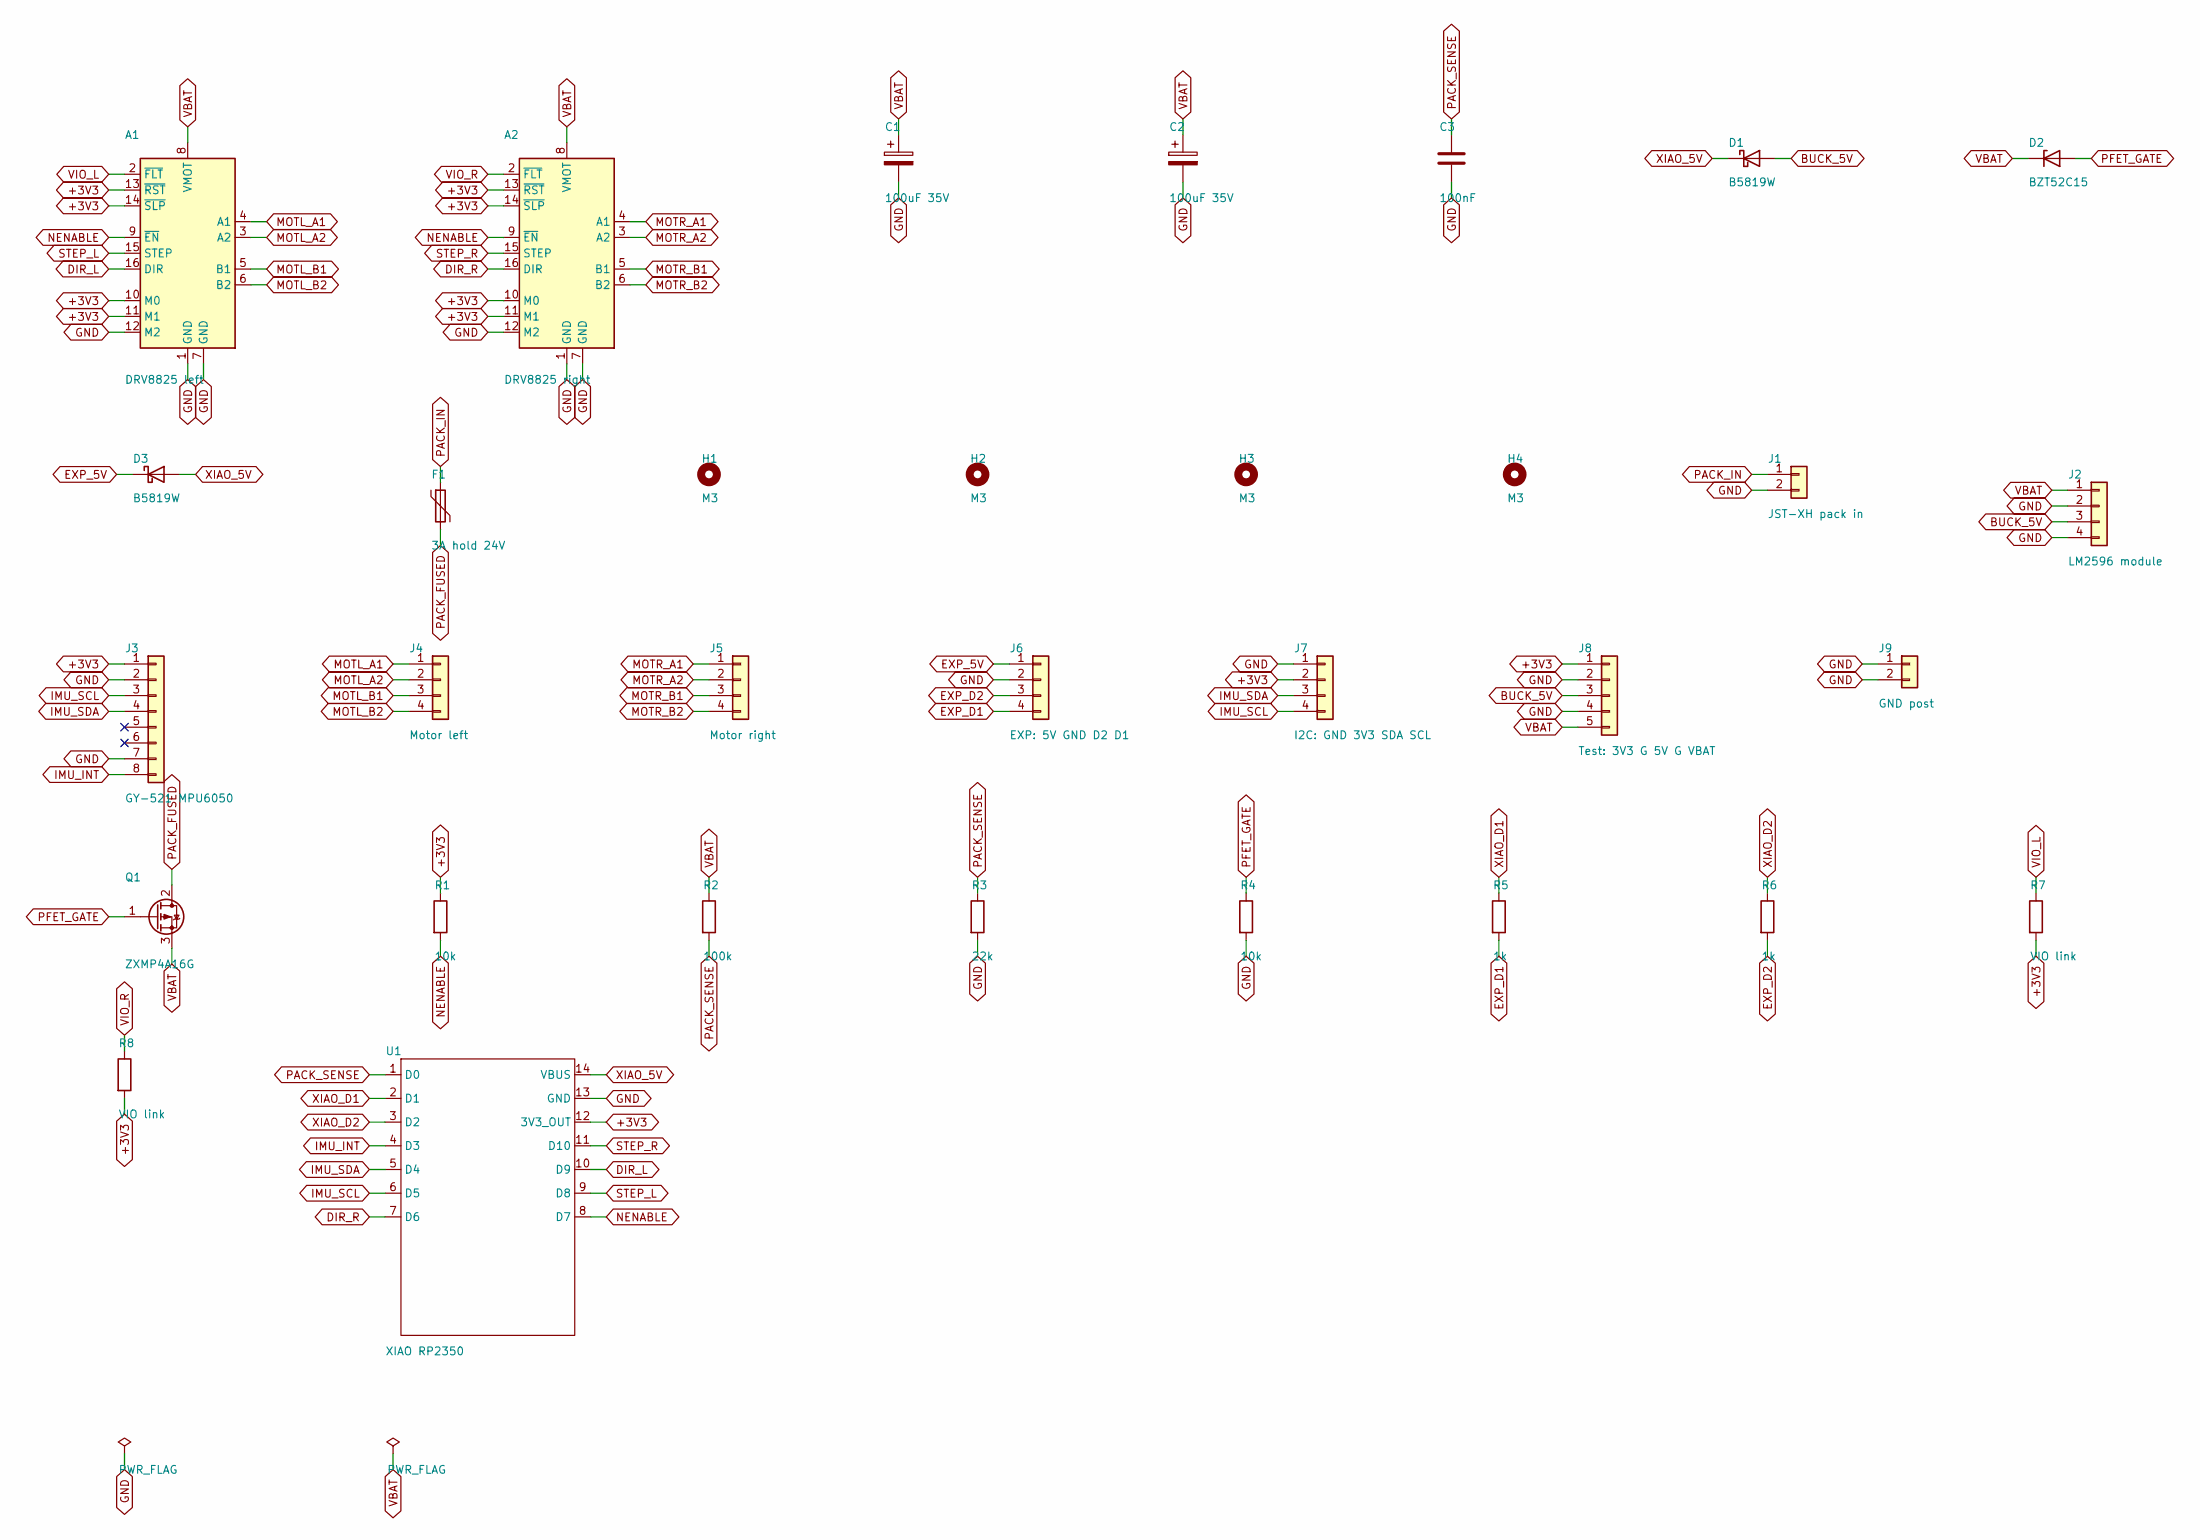
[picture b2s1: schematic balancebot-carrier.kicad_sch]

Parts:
A1: DRV8825 left; Pololu_Breakout-16_15.2x20.3mm
A2: DRV8825 right; Pololu_Breakout-16_15.2x20.3mm
C1, C2: 100uF 35V; CP_Elec_6.3x7.7; LCSC C2836437
C3: 100nF; C_0805_2012Metric_Pad1.18x1.45mm_HandSolder; LCSC C49678
D1, D3: B5819W; D_SOD-123; LCSC C8598
D2: BZT52C15; D_SOD-123; LCSC C2104
F1: 3A hold 24V; Fuse_1812_4532Metric_Pad1.30x3.40mm_HandSolder; LCSC C7500481
H1, H2, H3, H4: M3; MountingHole_3.2mm_M3
J1: JST-XH pack in; JST_XH_B2B-XH-A_1x02_P2.50mm_Vertical
J2: LM2596 module; JST_XH_B4B-XH-A_1x04_P2.50mm_Vertical
J3: GY-521 MPU6050; GY521_Socket
J4: Motor left; JST_XH_B4B-XH-A_1x04_P2.50mm_Vertical
J5: Motor right; JST_XH_B4B-XH-A_1x04_P2.50mm_Vertical
J6: EXP: 5V GND D2 D1; PinHeader_1x04_P2.54mm_Vertical
J7: I2C: GND 3V3 SDA SCL; PinHeader_1x04_P2.54mm_Vertical
J8: Test: 3V3 G 5V G VBAT; PinHeader_1x05_P2.54mm_Vertical
J9: GND post; PinHeader_1x02_P2.54mm_Vertical
Q1: ZXMP4A16G; SOT-223-3_TabPin2; LCSC C141324
R1, R4: 10k; R_0805_2012Metric_Pad1.20x1.40mm_HandSolder; LCSC C17414
R2: 100k; R_0805_2012Metric_Pad1.20x1.40mm_HandSolder; LCSC C149504
R3: 22k; R_0805_2012Metric_Pad1.20x1.40mm_HandSolder; LCSC C17560
R5, R6: 1k; R_0805_2012Metric_Pad1.20x1.40mm_HandSolder; LCSC C17513
R7, R8: VIO link; R_0805_2012Metric_Pad1.20x1.40mm_HandSolder
U1: XIAO RP2350; XIAO-RP2350-Socket

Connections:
+3V3: A1.10 (M0), A1.11 (M1), A1.13 (~RST), A1.14 (~SLP), A2.10 (M0), A2.11 (M1), A2.13 (~RST), A2.14 (~SLP), J3.1, J7.2, J8.1, R1.1, R7.2, R8.2, U1.12 (3V3_OUT)
BUCK_5V: D1.2 (A), J2.3, J8.3
DIR_L: A1.16 (DIR), U1.10 (D9)
DIR_R: A2.16 (DIR), U1.7 (D6)
EXP_5V: D3.1 (K), J6.1
EXP_D1: J6.4, R5.2
EXP_D2: J6.3, R6.2
GND: A1.1 (GND), A1.7 (GND), A1.12 (M2), A2.1 (GND), A2.7 (GND), A2.12 (M2), C1.2, C2.2, C3.2, J1.2, J2.2, J2.4, J3.2, J3.7, J6.2, J7.1, J8.2, J8.4, J9.1, J9.2, R3.2, R4.2, U1.13 (GND)
IMU_INT: J3.8, U1.4 (D3)
IMU_SCL: J3.3, J7.4, U1.6 (D5)
IMU_SDA: J3.4, J7.3, U1.5 (D4)
MOTL_A1: A1.4 (A1), J4.1
MOTL_A2: A1.3 (A2), J4.2
MOTL_B1: A1.5 (B1), J4.3
MOTL_B2: A1.6 (B2), J4.4
MOTR_A1: A2.4 (A1), J5.1
MOTR_A2: A2.3 (A2), J5.2
MOTR_B1: A2.5 (B1), J5.3
MOTR_B2: A2.6 (B2), J5.4
NENABLE: A1.9 (~EN), A2.9 (~EN), R1.2, U1.8 (D7)
PACK_FUSED: F1.2, Q1.2 (D)
PACK_IN: F1.1, J1.1
PACK_SENSE: C3.1, R2.2, R3.1, U1.1 (D0)
PFET_GATE: D2.2 (A), Q1.1 (G), R4.1
STEP_L: A1.15 (STEP), U1.9 (D8)
STEP_R: A2.15 (STEP), U1.11 (D10)
VBAT: A1.8 (VMOT), A2.8 (VMOT), C1.1, C2.1, D2.1 (K), J2.1, J8.5, Q1.3 (S), R2.1
VIO_L: A1.2 (~FLT), R7.1
VIO_R: A2.2 (~FLT), R8.1
XIAO_5V: D1.1 (K), D3.2 (A), U1.14 (VBUS)
XIAO_D1: R5.1, U1.2 (D1)
XIAO_D2: R6.1, U1.3 (D2)
